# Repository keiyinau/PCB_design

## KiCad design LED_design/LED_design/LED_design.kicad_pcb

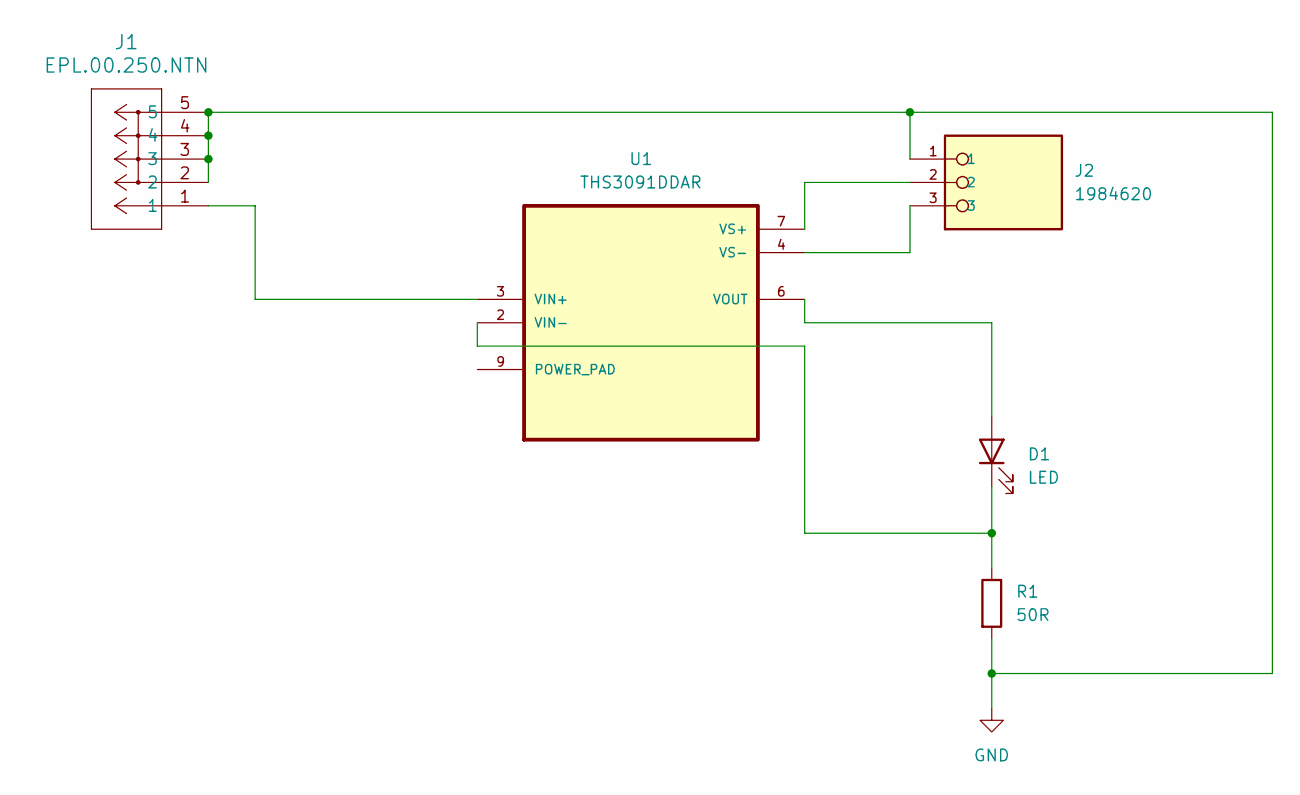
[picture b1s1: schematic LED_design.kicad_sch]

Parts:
D1: LED; LED_D2.0mm_W4.8mm_H2.5mm_FlatTop
J1: EPL.00.250.NTN
J2: 1984620; CONN_1984620_PXC
R1: 50R; R_0402_1005Metric
U1: THS3091DDAR; VREG_LM5017MR_NOPB

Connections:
GND: J1.2, J1.3, J1.4, J1.5, J2.1, R1.2
unnamed: D1.2 (A), U1.6 (VOUT)
unnamed: D1.1 (K), R1.1, U1.2 (VIN-)
unnamed: J1.1, U1.3 (VIN+)
unnamed: J2.2, U1.7 (VS+)
unnamed: J2.3, U1.4 (VS-)

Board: 2 copper layers, 5 parts (0 on the bottom side), 6 nets, no tracks yet.

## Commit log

2026-02-04 First init
2026-02-05 fwaipeghoiwe
2026-02-05 Modified HellowWorld
